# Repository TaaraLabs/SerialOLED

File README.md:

Serial OLED
===========

Small adapter board for 0,9" i2c OLED modules to be used as a 3.3V serial console.

[WebSite](https://taaralabs.eu/so1)

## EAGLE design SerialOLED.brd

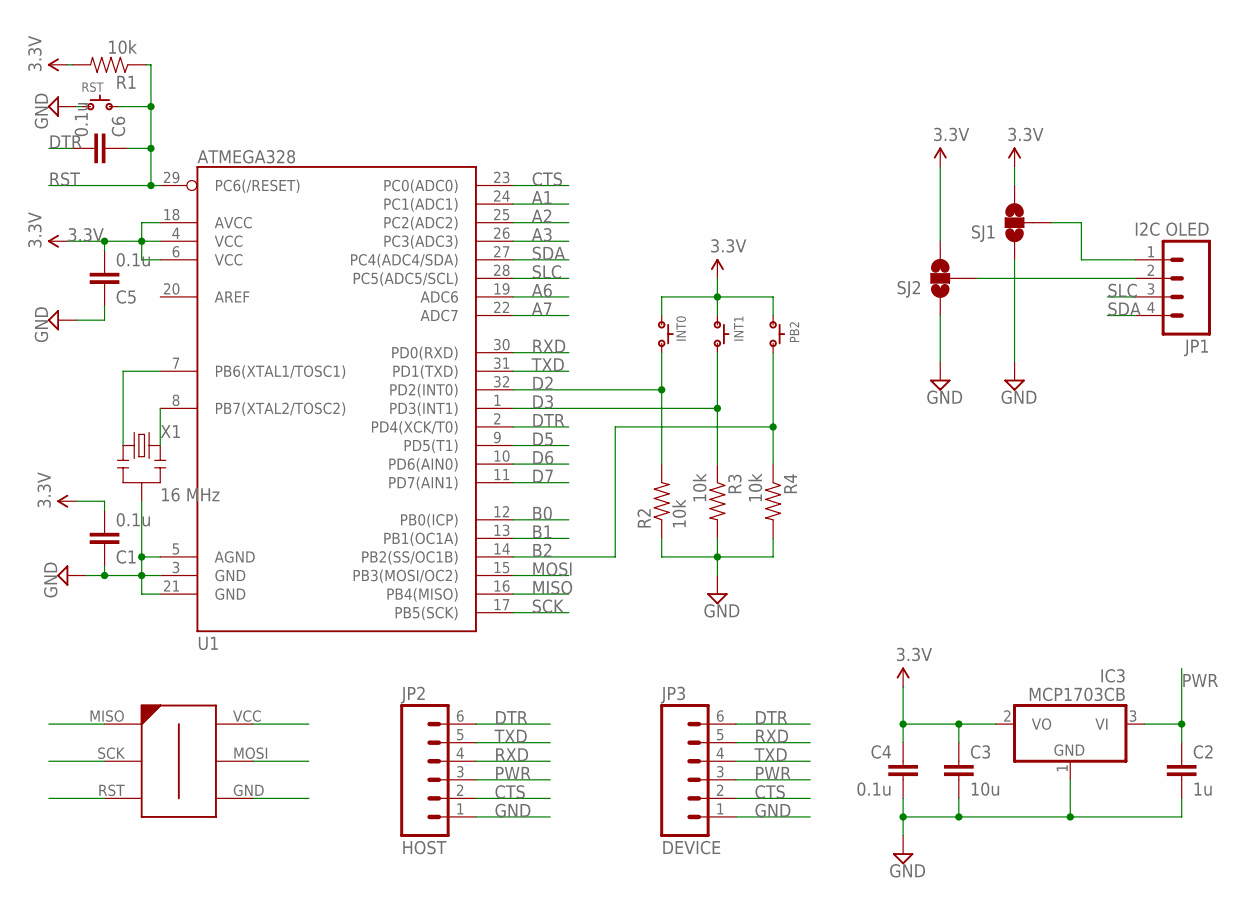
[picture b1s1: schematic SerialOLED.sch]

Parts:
C1, C4, C5, C6: 0.1u; 0603-CAP
C2: 1u; 0603-CAP
C3: 10u; 0805
IC3: MCP1703CB; SOT23
INT0, INT1: SPST.B3U-3000P(M)-B; B3U-3000P(M)-B
JP1: I2C OLED; 1X04_LOCK
JP2: HOST; 1X06-SIP_LOCK
JP3: DEVICE; 1X06-SIP_LOCK
PB2: SPST.B3U-3000P(M)-B; B3U-3000P(M)-B
R1, R2, R3, R4: 10k; 0603-RES
RST: SPST.B3U-3000P(M)-B; B3U-3000P(M)-B
SJ1: SOLDERJUMPER_2WAYPASTE1&2; SJ_3_PASTE1&2
SJ2: SOLDERJUMPER_2WAYPASTE2&3; SJ_3_PASTE2&3
U1: ATMEGA328; TQFP32-08
U$6: AVR-ISP-6-EDGE; 6PAD_ISP
X1: 16 MHz; RESONATOR-SMD

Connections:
3.3V: C1.2, C3.1, C4.1, C5.2, IC3.2 (VO), INT0.1, INT1.2, PB2.1, R1.2, SJ1.3, SJ2.3, U1.4 (VCC), U1.6 (VCC), U1.18 (AVCC), U$6.VCC
A1: U1.24 (PC1(ADC1))
A2: U1.25 (PC2(ADC2))
A3: U1.26 (PC3(ADC3))
A6: U1.19 (ADC6)
A7: U1.22 (ADC7)
B0: U1.12 (PB0(ICP))
B1: U1.13 (PB1(OC1A))
B2: PB2.2, R4.1, U1.14 (PB2(SS/OC1B))
CTS: JP2.2, JP3.2, U1.23 (PC0(ADC0))
D2: INT0.2, R2.2, U1.32 (PD2(INT0))
D3: INT1.1, R3.1, U1.1 (PD3(INT1))
D5: U1.9 (PD5(T1))
D6: U1.10 (PD6(AIN0))
D7: U1.11 (PD7(AIN1))
DTR: C6.2, JP2.6, JP3.6, U1.2 (PD4(XCK/T0))
GND: C1.1, C2.2, C3.2, C4.2, C5.1, IC3.1 (GND), JP2.1, JP3.1, R2.1, R3.2, R4.2, RST.1, SJ1.1, SJ2.1, U1.3 (GND), U1.5 (AGND), U1.21 (GND), U$6.GND, X1.2
MISO: U1.16 (PB4(MISO)), U$6.MISO
MOSI: U1.15 (PB3(MOSI/OC2)), U$6.MOSI
unnamed: U1.7 (PB6(XTAL1/TOSC1)), X1.1
unnamed: JP1.2, SJ2.2
unnamed: JP1.1, SJ1.2
unnamed: U1.8 (PB7(XTAL2/TOSC2)), X1.3
PWR: C2.1, IC3.3 (VI), JP2.3, JP3.3
RST: C6.1, R1.1, RST.2, U1.29 (PC6(/RESET)), U$6.RST
RXD: JP2.4, JP3.5, U1.30 (PD0(RXD))
SCK: U1.17 (PB5(SCK)), U$6.SCK
SDA: JP1.4, U1.27 (PC4(ADC4/SDA))
SLC: JP1.3, U1.28 (PC5(ADC5/SCL))
TXD: JP2.5, JP3.4, U1.31 (PD1(TXD))

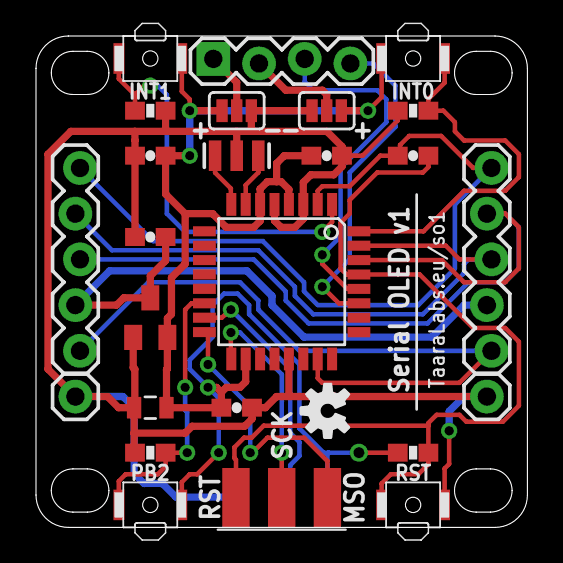
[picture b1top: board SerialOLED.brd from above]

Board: 2 copper layers, 27.3 x 27.3 mm, 25 parts (1 on the bottom side), 20 nets.

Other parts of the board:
U$1, U$2: OSHW-LOGO-S

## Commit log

2015-02-25 :neckbeard: Added .gitattributes
2015-02-25 Serial OLED
    Initial upload
2015-02-25 Solder-bridge for FTDI reset replaced with a capacitor
2015-02-25 New pictures
2015-05-04 Board fixes and new pictures

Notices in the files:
parts and their libraries:
SparkFun-Aesthetics: Licensing: CC v3.0 Share-Alike You are welcome to use this library for commercial purposes.
